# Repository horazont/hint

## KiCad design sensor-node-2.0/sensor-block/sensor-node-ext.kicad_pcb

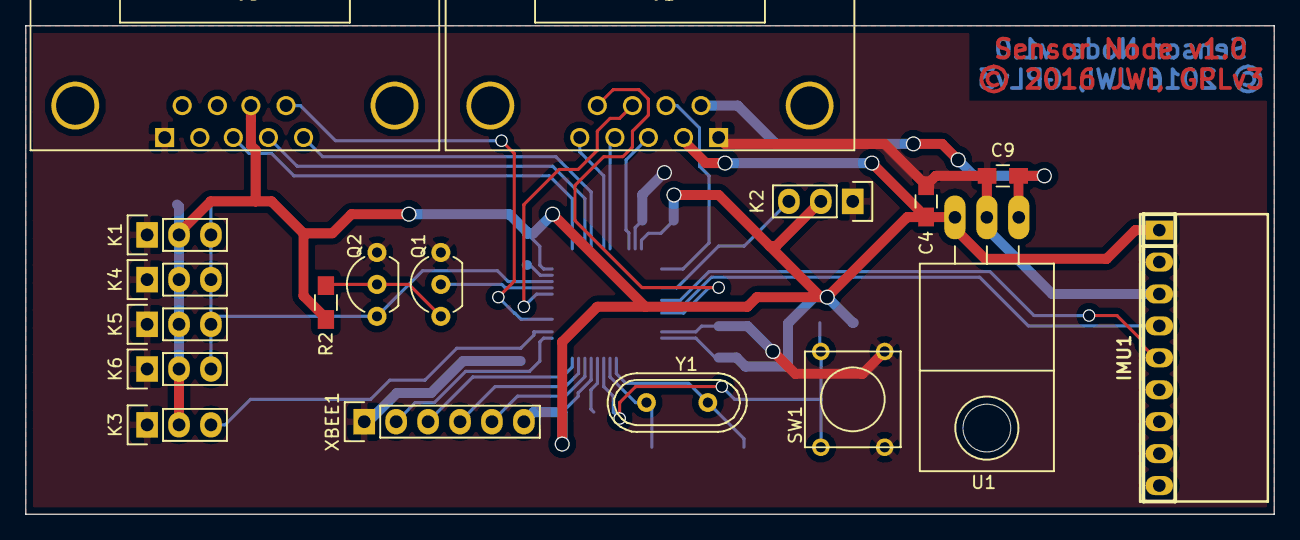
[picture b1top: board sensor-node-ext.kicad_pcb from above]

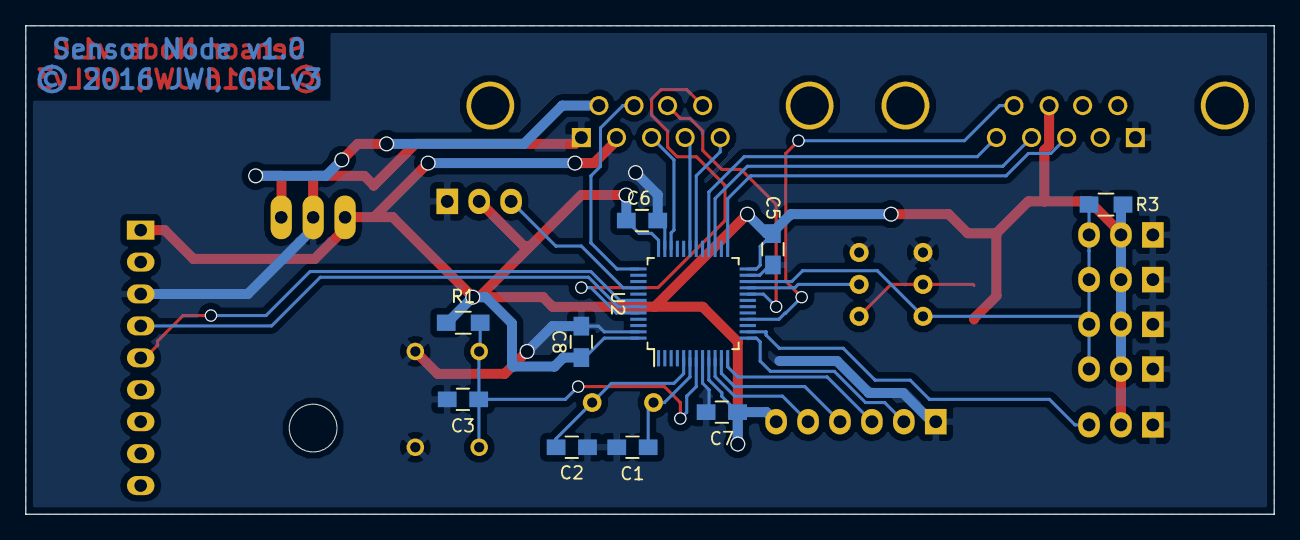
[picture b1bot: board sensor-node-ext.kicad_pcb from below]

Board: 2 copper layers, 99.3 x 38.9 mm, 28 parts (10 on the bottom side), 27 nets.

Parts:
C1, C2: 56p; C_0805_HandSoldering
C3, C5, C6, C7, C8: 100n; C_0805_HandSoldering
C4, C9: 10u; C_0805_HandSoldering
IMU1: IMU; pin_socket_9
J1: DB9; DB9MC
J3: DB9; DB9FC
K1, K2, K3, K4, K5, K6: XLR3; Pin_Header_Straight_1x03
Q1, Q2: BS170; TO-92_Inline_Wide
R1, R2: 100k; R_0805_HandSoldering
R3: 4.7k; R_0805_HandSoldering
SW1: SW_PUSH; SW_PUSH_SMALL
U1: TS2940-CZ33; TO-220_Neutral123_Horizontal_LargePads
U2: STM32F103CB; LQFP-48_7x7mm_Pitch0.5mm
XBEE1: XBEE; Pin_Header_Straight_1x06
Y1: 24MHz; Crystal_HC49-U_Vertical

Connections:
+3V3: C4.1, C5.1, C6.1, C7.1, C8.1, IMU1.1, J1.2, J3.8, K1.2, K2.2, K3.2, K4.2, K5.2, K6.2, R1.1, R2.1, R3.1, U1.3, U2.9, U2.24, U2.36, U2.48, XBEE1.6
+5V: C9.1, J1.6, U1.1
/Sensor Block/BOOT0: J1.9, U2.44
/Sensor Block/BOOT1: J1.8, U2.20
/Sensor Block/DHT_BUS: K2.3, U2.40
/Sensor Block/IMU_SCL: IMU1.5, U2.42
/Sensor Block/IMU_SDA: IMU1.4, U2.43
/Sensor Block/LIGHT1_EN: J3.3, U2.25
/Sensor Block/LIGHT1_FREQ: J3.9, U2.16
/Sensor Block/LIGHT1_SEL2: J3.4, U2.27
/Sensor Block/LIGHT1_SEL3: J3.5, U2.28
/Sensor Block/NOISE_LEVEL: K3.3, U2.14
/Sensor Block/RESET: C3.1, R1.2, SW1.2, U2.7
/Sensor Block/SWCLK: J1.7, U2.37
/Sensor Block/SWDIO: J1.3, U2.34
/Sensor Block/USART1_RX: J1.4, U2.31
/Sensor Block/USART1_TX: J1.5, U2.30
/Sensor Block/USART To OneWire/ONEWIRE_BUS: K1.3, K4.3, K5.3, K6.3, Q2.1, R3.2, U2.22
/Sensor Block/USART To OneWire/USART_TX: Q1.2, U2.21
/Sensor Block/USART To OneWire/nUSART_TX: Q1.1, Q2.2, R2.2
/Sensor Block/XBEE_CTS: U2.10, XBEE1.5
/Sensor Block/XBEE_RTS: U2.11, XBEE1.4
/Sensor Block/XBEE_RX: U2.13, XBEE1.2
/Sensor Block/XBEE_TX: U2.12, XBEE1.3
/Sensor Block/XTAL1: C1.1, U2.6, Y1.1
/Sensor Block/XTAL2: C2.1, U2.5, Y1.2
GND: C1.2, C2.2, C3.2, C4.2, C5.2, C6.2, C7.2, C8.2, C9.2, IMU1.3, J1.1, J3.1, K1.1, K2.1, K3.1, K4.1, K5.1, K6.1, Q1.3, Q2.3, SW1.1, U1.2, U2.8, U2.23, U2.35, U2.47, XBEE1.1

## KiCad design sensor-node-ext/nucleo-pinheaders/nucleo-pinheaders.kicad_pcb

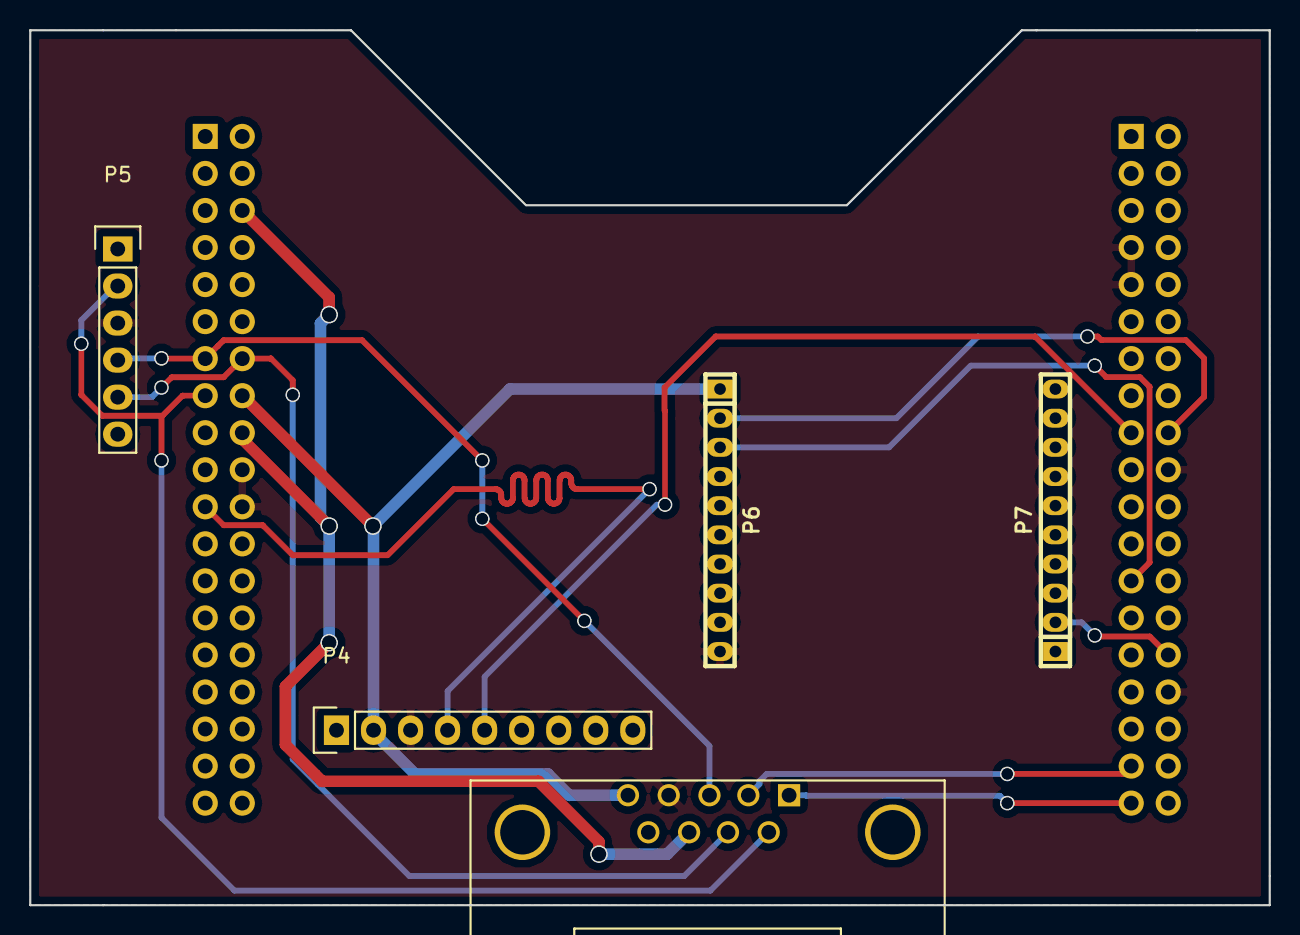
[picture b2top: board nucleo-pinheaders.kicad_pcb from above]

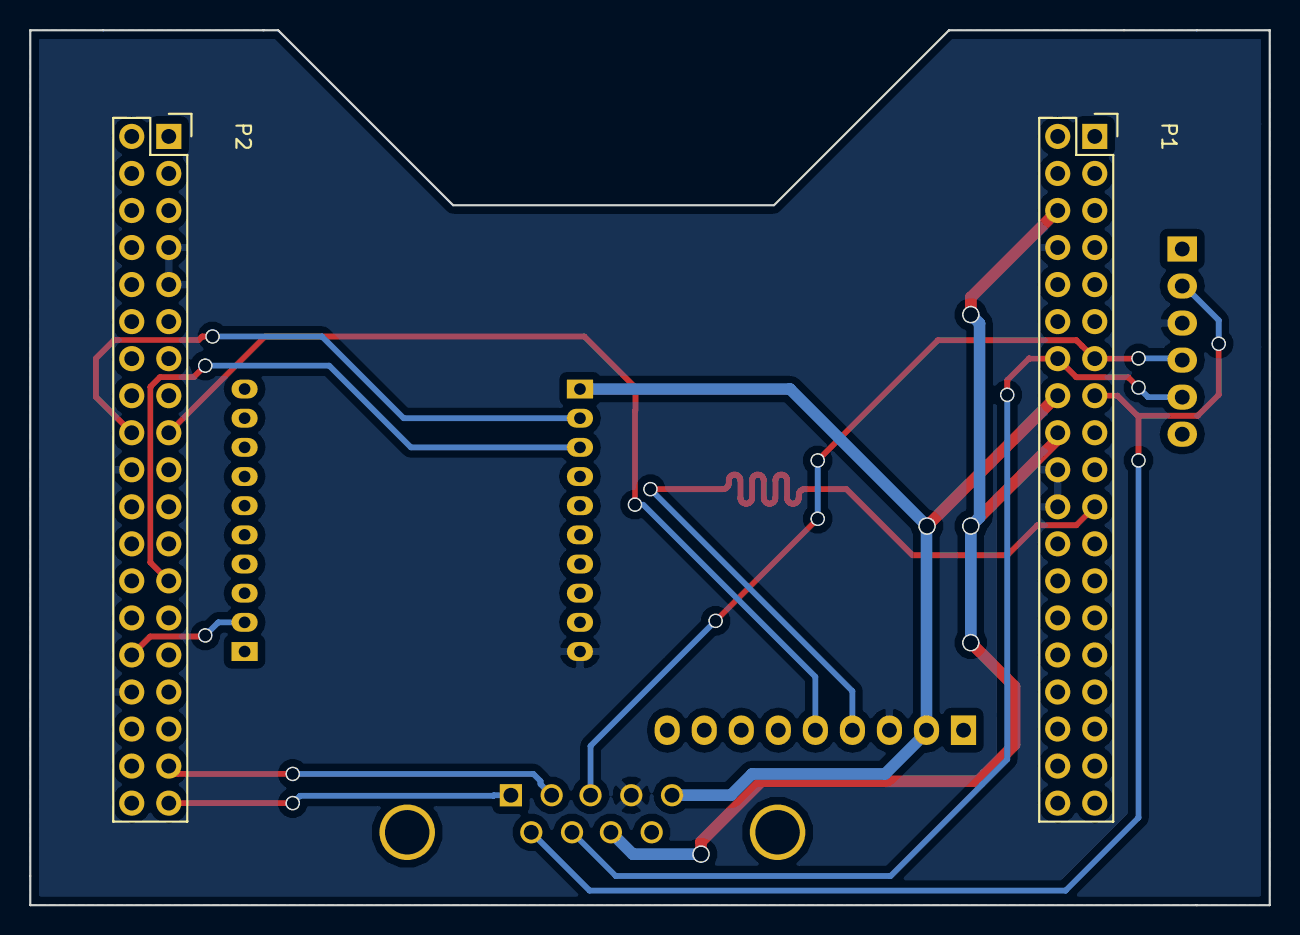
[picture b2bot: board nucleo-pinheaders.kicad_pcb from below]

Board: 2 copper layers, 85.0 x 60.0 mm, 7 parts (2 on the bottom side), 13 nets.

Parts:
J1: DB9; DB9FC
P1, P2: CONN_02X19; Socket_Strip_Straight_2x19
P4: CONN_01X09; Socket_Strip_Straight_1x09
P5: CONN_01X06; Pin_Header_Straight_1x06
P6: XBEEL; pin_socket_2mm_10
P7: XBEER; pin_socket_2mm_10

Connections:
+3V3: J1.5, P1.16, P4.2, P6.1
+5V: J1.8, P1.6, P1.18
/I2C1_N: P2.17, P4.5
/I2C1_P: P1.21, P4.4
/RESET: J1.7, P1.14, P5.5
/SWCLK: J1.6, P1.15, P5.2
/SWDIO: J1.3, P1.13, P5.4
/USART2_RX: J1.1, P2.37
/USART2_TX: J1.2, P2.35
/USART3_CTS: P2.30, P7.2
/USART3_RX: P2.18, P6.2
/USART3_TX: P2.25, P6.3
GND: J1.4, P1.8, P1.20, P1.22, P2.7, P2.9, P2.20, P2.32, P4.3, P5.3, P6.10

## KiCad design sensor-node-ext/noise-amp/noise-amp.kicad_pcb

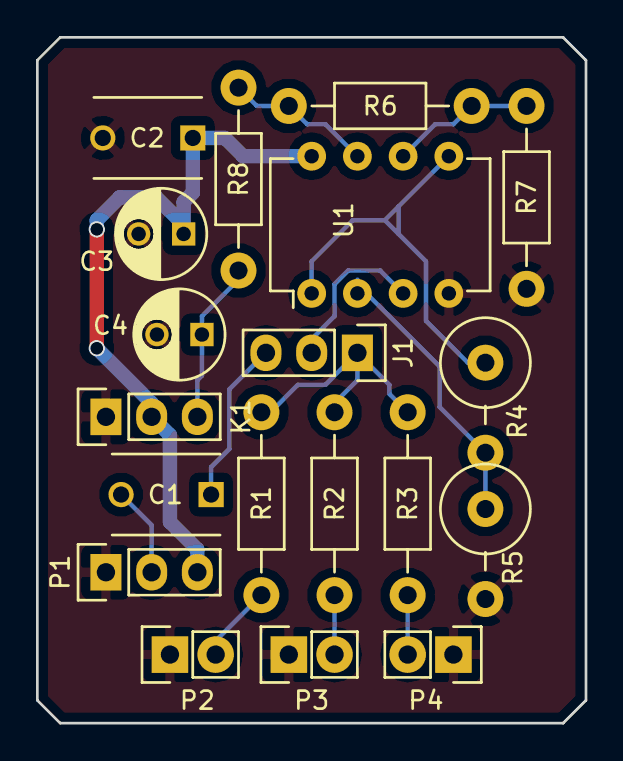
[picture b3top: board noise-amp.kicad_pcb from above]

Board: 2 copper layers, 30.5 x 38.1 mm, 19 parts (0 on the bottom side), 14 nets.

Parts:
C1, C2: C; C_Disc_D6_P5
C3, C4: CP; C_Radial_D5_L11_P2.5
J1: INSELECT; Pin_Header_Straight_1x03
K1: XLR3; Pin_Header_Straight_1x03
P1: MIC; Pin_Header_Straight_1x03
P2, P3, P4: PIEZO; Pin_Header_Straight_1x02
R1, R2, R3: 10k; Resistor_Horizontal_RM10mm
R4, R5: R; Resistor_Vertical_RM5mm
R6, R7, R8: R; Resistor_Horizontal_RM10mm
U1: MCP6002; DIP-8_W7.62mm

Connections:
+3V3: C2.1, C3.1, K1.2, P1.3, U1.8
GND: C2.2, C3.2, C4.2, K1.1, P1.1, P2.1, P3.1, P4.1, R5.2, R7.2, U1.4
unnamed: C1.1, J1.3
unnamed: C1.2, P1.2
unnamed: C4.1, K1.3, R8.1
unnamed: J1.1, R1.2, R2.2, R3.2
unnamed: J1.2, U1.3
unnamed: P2.2, R1.1
unnamed: P3.2, R2.1
unnamed: P4.2, R3.1
unnamed: R4.1, U1.1, U1.5
unnamed: R4.2, R5.1, U1.2
unnamed: R6.1, R8.2, U1.7
unnamed: R6.2, R7.1, U1.6

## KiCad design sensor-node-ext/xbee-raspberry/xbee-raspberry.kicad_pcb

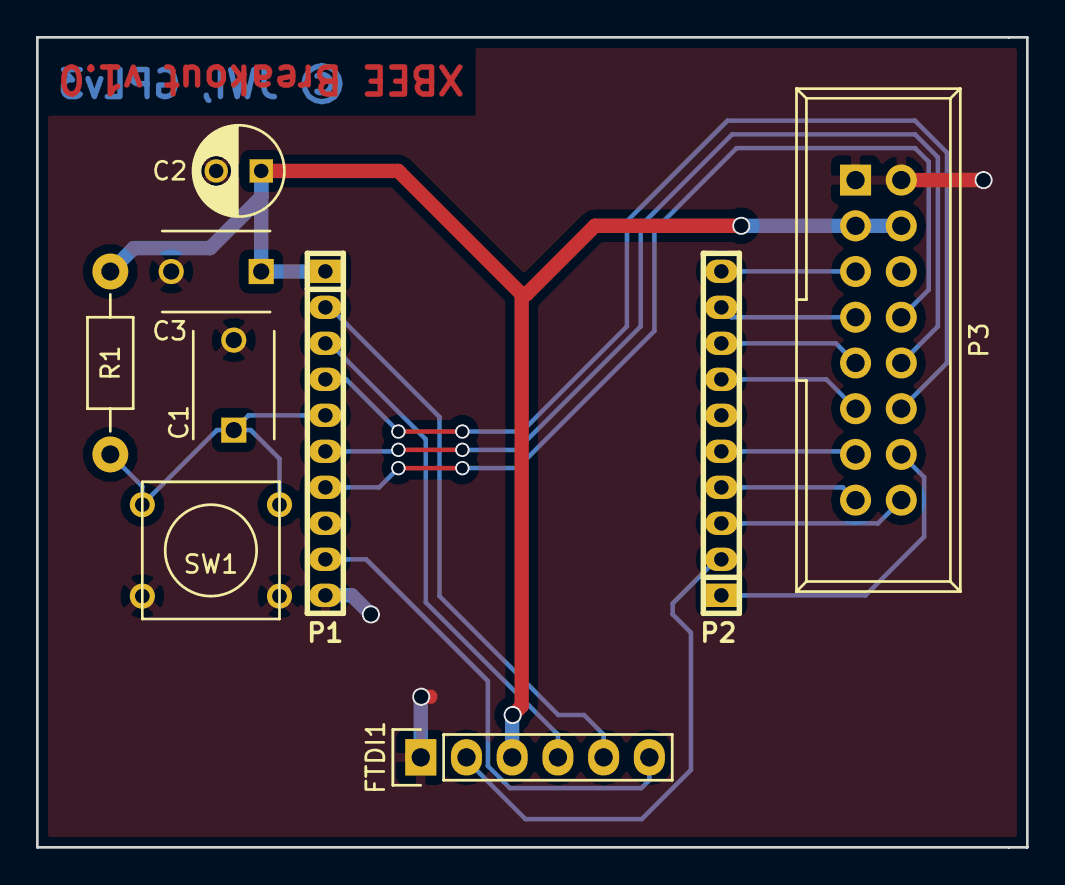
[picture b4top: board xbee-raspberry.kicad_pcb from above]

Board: 2 copper layers, 55.0 x 45.0 mm, 9 parts (0 on the bottom side), 18 nets.

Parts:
C1: 220n; C_Disc_D6_P5
C2: 1u; C_Radial_D5_L11_P2.5
C3: 8.2p; C_Disc_D6_P5
FTDI1: CONN_01X06; Pin_Header_Straight_1x06
P1, P2: CONN_01X10; pin_socket_2mm_10
P3: CONN_02X08; IDC_Header_Straight_16pins
R1: 4.7k; Resistor_Horizontal_RM10mm
SW1: SW_PUSH; SW_PUSH_SMALL

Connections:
+3V3: C2.1, C3.1, FTDI1.3, P1.1, P3.3, P3.4, R1.1
/AD0_DIO0: P2.10, P3.5
/AD1_DIO1: P2.9, P3.7
/AD2_DIO2: P2.8, P3.9
/AD3_DIO3: P2.7, P3.11
/CTS: FTDI1.2, P2.2
/DIO4: P2.1, P3.14
/DIO5: P2.5, P3.13
/DIO11: P1.7, P3.8
/DIO12: P1.4, P3.12
/DTR: FTDI1.6, P1.9
/ON: P2.3, P3.16
/RESET: C1.1, P1.5, R1.2, SW1.2
/RSSIPWM_DIO10: P1.6, P3.10
/RX: FTDI1.5, P1.2
/TX: FTDI1.4, P1.3
/VREF: P2.4, P3.15
GND: C1.2, C2.2, C3.2, FTDI1.1, P1.10, P3.1, P3.2, SW1.1

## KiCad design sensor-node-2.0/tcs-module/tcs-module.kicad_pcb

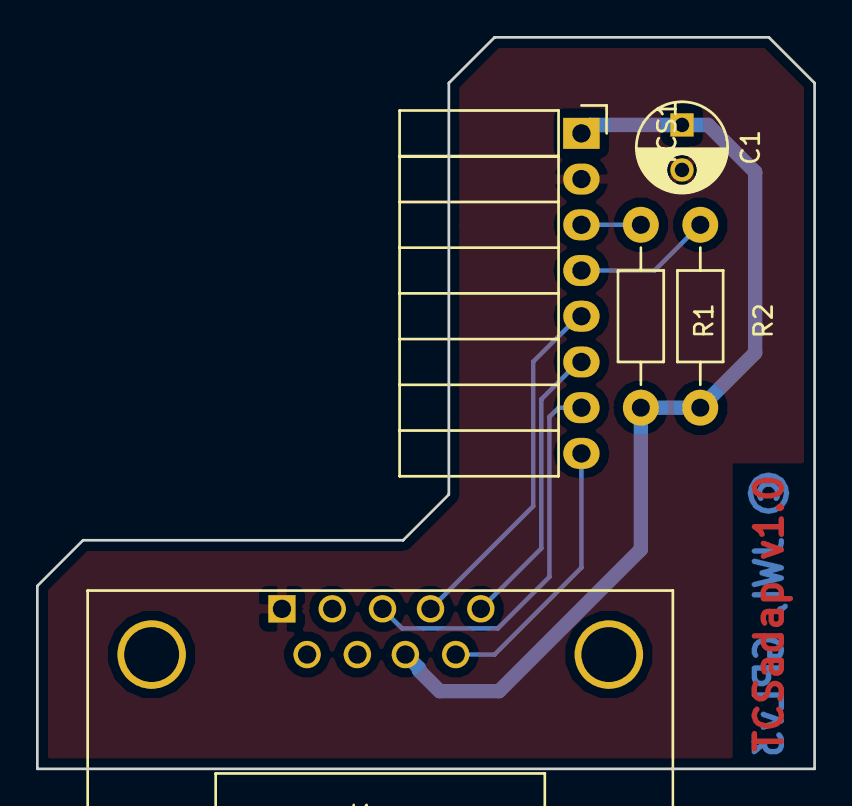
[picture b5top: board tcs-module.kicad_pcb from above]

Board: 2 copper layers, 43.2 x 40.6 mm, 5 parts (0 on the bottom side), 8 nets.

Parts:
C1: 1u; C_Radial_D5_L11_P2.5
J1: DB9; DB9MC
R1, R2: 4.7k; Resistor_Horizontal_RM10mm
TCS1: CONN_01X08; Socket_Strip_Angled_1x08

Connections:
+3V3: C1.1, J1.8, R1.2, R2.2, TCS1.1
/EN: J1.3, TCS1.7
/OUT: J1.9, TCS1.8
/S2: J1.4, TCS1.5
/S3: J1.5, TCS1.6
GND: C1.2, J1.1, TCS1.2
unnamed: R1.1, TCS1.3
unnamed: R2.1, TCS1.4

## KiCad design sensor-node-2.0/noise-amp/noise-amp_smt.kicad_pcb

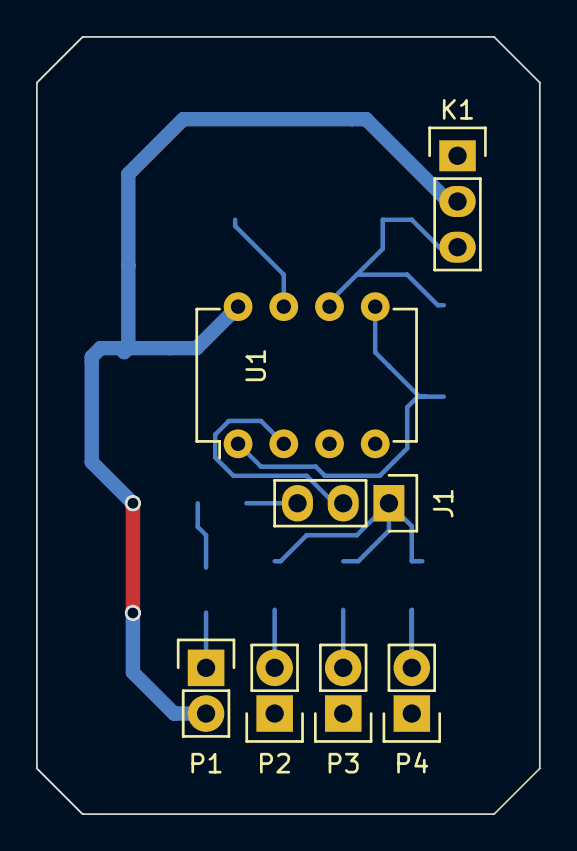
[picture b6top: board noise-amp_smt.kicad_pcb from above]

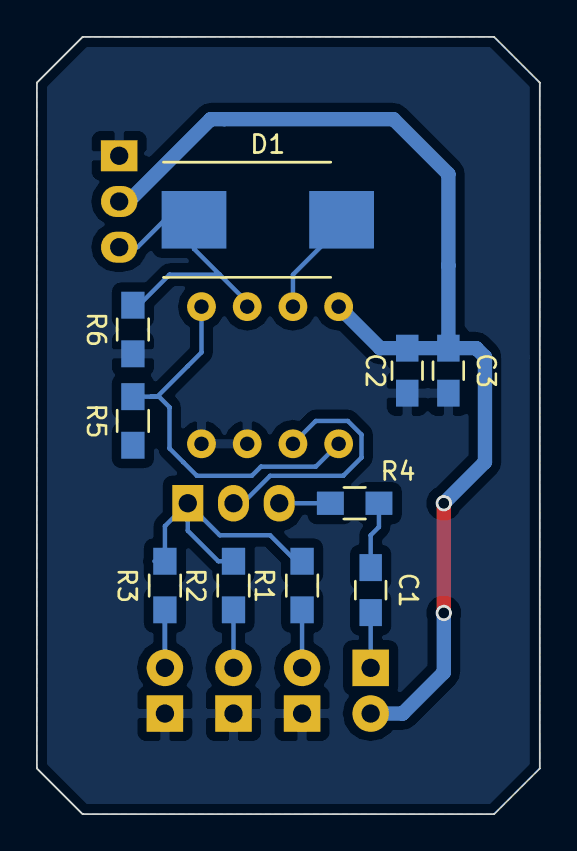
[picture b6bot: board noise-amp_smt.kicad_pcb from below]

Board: 2 copper layers, 27.9 x 43.2 mm, 17 parts (10 on the bottom side), 13 nets.

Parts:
C1, C2: C; C_0805_HandSoldering
C3: CP; C_0805_HandSoldering
D1: D; DO-214AB_Handsoldering
J1: INSELECT; Pin_Header_Straight_1x03
K1: XLR3; Pin_Header_Straight_1x03
P1: MIC; Pin_Header_Straight_1x02
P2, P3, P4: PIEZO; Pin_Header_Straight_1x02
R1, R2, R3, R4: 10k; R_0805_HandSoldering
R5: 100k; R_0805_HandSoldering
R6: R; R_0805_HandSoldering
U1: MCP6002; DIP-8_W7.62mm

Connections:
+3V3: C2.1, C3.1, K1.2, P1.2, U1.8
GND: C2.2, C3.2, K1.1, P2.1, P3.1, P4.1, R6.2, U1.3, U1.4
unnamed: C1.1, R4.2
unnamed: C1.2, P1.1
unnamed: D1.1, K1.3, R6.1, U1.6
unnamed: D1.2, U1.7
unnamed: J1.1, R1.2, R2.2, R3.2
unnamed: J1.2, R5.2, U1.2
unnamed: J1.3, R4.1
unnamed: P2.2, R1.1
unnamed: P3.2, R2.1
unnamed: P4.2, R3.1
unnamed: R5.1, U1.1, U1.5

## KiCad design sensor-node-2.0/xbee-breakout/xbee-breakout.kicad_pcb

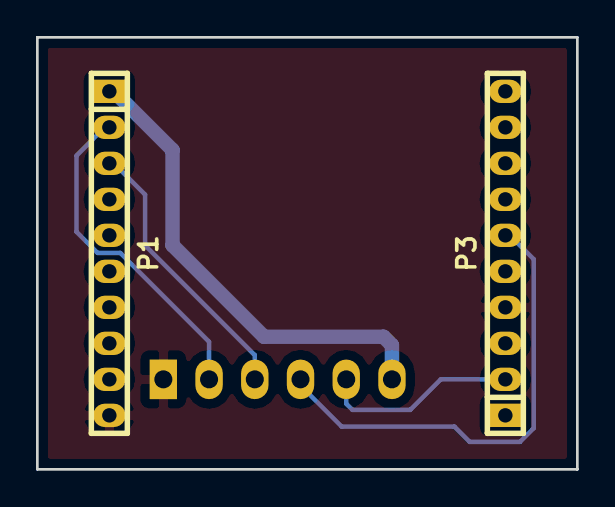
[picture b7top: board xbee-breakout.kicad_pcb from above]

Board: 2 copper layers, 30.0 x 24.0 mm, 3 parts (1 on the bottom side), 6 nets.

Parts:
P1, P3: CONN_01X10; pin_socket_2mm_10
P2: CONN_01X06; pin_socket_6

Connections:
+3V3: P1.1, P2.6
/XBEE_CTS: P2.5, P3.2
/XBEE_DIN: P1.3, P2.3
/XBEE_DOUT: P1.2, P2.2
/XBEE_RTS: P2.4, P3.6
GND: P1.10, P2.1, P3.4

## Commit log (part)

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2013-11-02 Setup build environment for display code
2013-11-03 Make a useful basic template
2013-11-03 First draw commands
2013-11-03 Use proper set operations (ty, SRI)
2013-11-04 Fix sorting of functions in lcd.c
2013-11-04 Optimize makefile
2013-11-04 Use setpixel
2013-11-04 Inline some more functions
2013-11-04 Always include replacement character
2013-11-04 Port to codepoint ranges
2013-11-04 Fix indentation in generated font file
2013-11-05 Add option to store font in a given ELF section
2013-11-05 Store font in .text section
2013-11-05 Support for boldface fonts
2013-11-05 Support for font size in pixels
2013-11-05 Build more fonts
2013-11-05 Fix UTF8 decoder
2013-11-07 Implement preliminary graph library
2013-11-07 TEMPORARY
2013-11-07 Fix incorrect offset in graph axis drawing
2013-11-07 Implement table engine
2013-11-10 Add macros for storage locations
2013-11-10 Move coord ints to lcd
2013-11-10 Add missing ADC_READ helper
2013-11-10 Implement a custom UART library with routing
2013-11-12 Reimplement comm library
    This version takes proper care of locking the TX unit so that no two
    TXes happen at the same time.
2013-11-13 Split up comm.c into smaller subfiles
2013-11-20 Bootstrap host code
2013-11-20 First communication code for hintd
2013-11-23 Change font face to DejaVu Sans
2013-11-23 Add option to export all glyphs to a directory
2013-11-23 Add flags field for control messages
2013-11-23 Add functions to transmit control messages
2013-11-23 Add function to push to the front of a queue
2013-11-23 Add handling of software flow control (ACK messages)
2013-11-23 Implement command handling on the LPC
2013-11-26 Simple dynamic memory management for the LPC
2013-11-26 Fix handling of buffer swap if backbuffer already has data
2013-11-26 Extend font library to return next character
    This allows chaining of font drawing commands for buffers which contain
    multiple NUL-separated strings.
2013-11-26 Fix calculation of text width
2013-11-26 Implement table column alignment
2013-11-26 Add function to draw table row from one buffer
2013-11-26 Add missing file: comm_internal.h
2013-11-26 genfont: add option to transpose glyph bitmaps
2013-11-26 Disable transparent drawing of font glyphs
    (This commit will be reverted immediately; it is here in case we need
    this variation later on again)
2013-11-26 Store font size in font_t
2013-11-26 Draw table rows with background
2013-11-26 Enable drawing of tables
2013-11-26 Skip touch events which are close together (noise reduction)
2013-11-26 Move source files in their own directory
2013-12-01 Move some types into common headers
2013-12-01 Add utilities to draw using the comm link
2013-12-01 Introduce common directory for utils
2013-12-01 Get rid of unused and deprecated variables
2013-12-01 Add array library
2013-12-01 Correctly pack table_column_t
2013-12-01 Stop drawing blue quads on touch events
2013-12-01 Add bold face series of 12px font
2013-12-01 Update and extend timestamp library
2013-12-01 Add library for drawing different screens
2013-12-02 Remove debug output
2013-12-02 Implement XMPP interface basement
2013-12-02 Implement preliminary handling of departure data
2013-12-05 Fix endianess issues
2013-12-05 Provide unified clock API, to ease porting
2013-12-05 Update CMake to be able to build for the fritzbox
2013-12-05 Process public transport data
2013-12-05 Reset UART state on timeout
2013-12-05 Make printing of messages portable
2013-12-05 Add initialization code
2013-12-05 Add utility to convert RGB24 (or float) values to RGB16
2013-12-08 Rework comm core to use pings to determine state of connection
2013-12-08 Fix checksum code
2013-12-09 Drop packages with checksum failures on LPC
2013-12-09 Add command to dynamically change backlight brightness
2013-12-09 Only repaint screen if comm is available
2013-12-09 Properly handle signalfd input
2013-12-09 Debugging instrumentation (do not pull)
2014-01-03 Work on weather service on display
2014-01-04 Implement pulling of departure data (instead of relying on push)
2014-01-04 More thread safety
2014-01-04 Send reset command on connect
2014-01-05 Use proper error handling for departure
2014-01-05 Implement clean shutdown and fix some memory leaks
2014-01-05 Add screen utilities
2014-01-05 Give screen_t access to broker_t
2014-01-05 Implement and mount MISC screen
2014-01-07 Fix missing screen_show event
2014-01-07 Implement networking screen
2014-01-12 Implement theme support
2014-01-12 Implement support for hex input in rgbto16
2014-01-12 Remove some debug output
2014-02-16 Catch http.client.BadStatusLine
2014-02-16 Improve build process for libcouplet
2014-02-16 Increase table width
2014-02-16 Implement smooth fading of display brightness
2014-02-16 Move backlight management into lcd.[hc]
2014-02-16 Reorder inlines in lcd.c
2014-02-17 Implement sleepout function in host code
2014-02-17 Fix memory leak and increase reconnect timeout
2014-02-17 Implement I2C beacon in arduino for testing
2014-02-18 Fix build issues with arduino
2014-03-13 Fix nightly crashes -- greetings from SIGPIPE
2014-03-13 Add debug output in shutdown phase
2014-03-13 Implement support for routing i2c to uart
2014-03-13 Embed OneWire library, version 2.2
    Credits for the library go to Paul Stoffregen, Jim Studt and others.
2014-03-14 Remove debug output buffer
2014-03-14 Implement collection and submission of sensor data in hintd
2014-03-14 Increase interval between two full samples to 10s
2014-03-14 Free mutex
2014-03-14 Add missing import
2014-03-14 Fix logging in dvb.py
2014-03-14 Gracefully handle rrdtool errors
2014-06-03 Fix cloudiness
2014-07-03 Add requester baseclass, to be used for APIs
    This one and for all implements exponential back off and caching.
2014-07-04 Add support for displaying age data on depature screen
2014-07-04 Let the implementation set the expiry of a CacheEntry
2014-07-04 Fix missing stop filters
2014-07-04 Fix typo
2014-07-04 Correctly handle back off situation
2014-07-04 Fix incorrect display of error messages
2014-07-04 Improve handling of aged data
2014-07-04 Add aggregation functionality to precipitation stanza
2014-07-04 Add support for multi-coord API services
2014-07-04 Implement support for fancy reliability display on dept screen
2014-07-04 Increase timeouts for IQ requests
2014-07-04 Request SI units
2014-07-05 Implement new weather screen
2014-07-05 Move hintbot.py into a __main__ for hintmodules
2014-07-05 Fix broken erasing of weather screen area before repaint
2014-07-05 Revert "Move hintbot.py into a __main__ for hintmodules"
    This reverts commit bf573cafecf8e3be4cb7e921f5163db8ed2a839a.
2014-07-08 Implement storage and retrieval of sensor values in hintbot
2014-07-08 Distinguish between raw point and point
2014-07-08 Add some logging
2014-07-08 Fix logging
2014-07-08 Read sensor values as floats
2014-07-14 Sort received sensor data by timestamp before storing
2014-08-27 Fix memory leak
2014-10-04 Initial commit (we have working bus enumeration!)
2014-10-04 Re-enable short-circuit in onewire_findnext
2014-10-06 We have working T sampling
2014-10-06 Add dedicated command to invoke temperature conversion
2014-10-07 Embed code from Atmel application note for TWI via USI
2014-10-07 Add function to read only the temperature from a sensor
2014-10-07 Add schematic for current onewire output stage
2014-10-08 Finalize sensor node firmware
2014-10-17 Add FIXME
2014-12-01 Add minus sign to 8px charset
    What a surprise that this winter was so mild until now :-O
2014-12-01 Use correct sign character for negative numbers
2014-12-01 Fix '3' glyph (and refactor genfont.py)
    We can now have glyphfiles which fully specify a glyph, instead of
    rendering a glyph using pango. This is useful if the renderer produces
    small uglinesses due to font size and hinting issues.
    Example is the '3' glyph with DejaVu Sans at 9px.
2014-12-07 Commit pending changes to sensor node schematic
2015-06-09 Add en dash to charset
2015-06-09 Fix memleaks and remove debug output
2015-06-09 Increase timeout for departure requests
2015-06-09 Return timestamp instead of age from hintbot
2015-06-09 Set correct attribute
2015-06-09 Fix response composition for departure requests
2015-06-09 Use nicer logging and error response message
2015-06-09 Remove extrapolation from dvb module (this is done in the client now)
2015-06-09 Increase timeout and catch empty result
2015-06-09 Filter by ETA on client side, too; fix calculation of ETA
2015-06-09 Update cmake files for new fritzbox version
2015-08-31 Fix handling of legacy service entries
2015-08-31 Use new MetNo API version
2015-11-20 Open TTY in non-blocking mode
2015-11-20 Clear comm queues also when entering open state
2016-02-10 Improve resilience of temperature measurement
2016-02-10 Provide facilities to debug reconnects to hint hardware
2016-05-28 Also read the port settings before re-writing them
2016-06-04 Minor cleanup
2016-06-04 Publish precipitation intensity on IQ response
2016-06-06 Cleanup
2016-06-06 Fix broken fix
2016-06-09 Request and visualise precipitation probability
2016-06-16 Comment unused declarations
2016-07-08 Work on sensor-node-ext schematics
2016-07-21 Sensor node ext designs
2016-10-11 Implement direction attribute on departure data
2017-05-19 Move to libstrophe
2017-05-19 Fix handling of flags
2017-05-26 Clean up sensor-node-ext data
2017-05-26 Add sensor-block firmware submodule
2017-05-26 Add gateway firmware
2017-05-30 Commit new hintd draft
2017-05-30 Cleanup hintbot directory a bit
2017-05-30 Clean up hostpy directory
2017-05-30 Make comm headers compatible with CFFI
2017-05-30 Improve debug output
2017-05-30 Clean up display directory
2017-05-30 Rename sensor-node-ext to sensor-node-2.0
2017-10-13 Update git modules
2018-02-26 Add bot library stuff
2018-04-27 Do not show zero numbers in weather screen
2018-04-28 Fix threshold for showing precip prob.
2020-03-28 hostpy: support for DVB departure view
2020-03-30 Extend hostpy
2020-03-30 Colourize humidity sensor
2020-03-30 Use 12px font for sensor group heading
    The 9px font doesn’t have all characters we need and I’m too lazy
    to build a new image.
2020-03-30 Terminate stream if a message goes un-ACK-ed
    This is to force a reset.
2020-03-30 Set the brightness after waking up from sleep
2020-03-30 Use configurable timezone for clock display
2020-09-23 Change departure plugin to use another API endpoint
2020-11-01 Work on smbusd
2020-11-03 Replace smbusd by a generic metric relay service
2021-06-30 Implement covid panel
2021-06-30 Left-align covid table header
2021-07-04 Add very important module
2021-07-12 covid: draw a nice chart
2022-01-09 Update doofescovid.de query
2022-01-09 Fix sign error in number formatting
    We are adding a proper minus (U+2013) instead of a normal -, so we must
    strip it from the actual number formatting.
2022-11-01 display: Fix inconsistent indentation in the makefile
2022-11-01 display: Add fallthrough annotations to make gcc happy
    * The code is built with -Werror and newer gccs warn on implicit
    fallthrough with -Wall -Wextra, so the build failed.
2022-11-04 Forward touch events to screens
2022-11-04 Add new button screen
2022-11-04 Port faked to qasync
2022-11-04 Improve resilience in departure module
2022-11-09 display: Fix make -B
    * make -B did not work, because ln -s failed on existing links –
    fixed by using -f.
2022-11-09 display: Remove unused variables
2026-05-08 Add support for querying influxdb servers
2026-05-08 Add support for trimming influxdb query results
2026-05-09 Do not show outdated sensor data as recent

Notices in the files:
sensor-node-2.0/sensor-block/sensor-node-ext.kicad_pcb:
© 2016 JWI, GPLv3
sensor-node-2.0/tcs-module/tcs-module.kicad_pcb:
© JWI, GPLv3
